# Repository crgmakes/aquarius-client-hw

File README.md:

# Aquarius Client Hardware

All the source files for the client hardware.

# Software 

You will need [KiCad](https://kicad.org) to view and edit this design. Click [here](https://www.kicad.org/download/) to download.

You will also need all the associated libraries and models to drive the design if you want to make changes or view the 3D rendering:

https://github.com/crgmakes/kicad-library.git

Kicad MUST be configured properly to use all the files in this repo. Once you have Kicad installed, under Preferences->Configure Paths..., make the following entries:

1 - KICAD_USER_DIR -> set to the root location of where you placed the above repository.
2 - KICAD_USER_LIBRARY = ${KICAD_USER_DIR}/Library
3 - KICAD_USER_MODEL_DIR = ${KICAD_USER_LIBRARY}/models
4 - KICAD_USER_TEMPLATE_DIR	= ${KICAD_USER_LIBRARY}/templates	

Kicad will operate mostly normally if these are not set properly. You will notice an issue when you view the PCB in 3D mode.

***NOTE***: after makeing a release build in git, if your rendered 3D images are missing components, ensure the path to EVERY component model is set to ${KICAD_USER_MODEL_DIR}/<model name>.

Kicad sometimes replaces the variable with an expansion and that FAILS during the build process because the expanded variable is local and does not match the build environment.

---

THE DESIGN IS PROVIDED "AS IS" AND THE AUTHOR DISCLAIMS ALL WARRANTIES WITH REGARD TO THIS DESIGN INCLUDING ALL IMPLIED WARRANTIES OF MERCHANTABILITY AND FITNESS. IN NO EVENT SHALL THE AUTHOR BE LIABLE FOR ANY SPECIAL, DIRECT, INDIRECT, OR CONSEQUENTIAL DAMAGES OR ANY DAMAGES WHATSOEVER RESULTING FROM LOSS OF USE, DATA OR PROFITS, WHETHER IN AN ACTION OF CONTRACT, NEGLIGENCE OR OTHER TORTIOUS ACTION, ARISING OUT OF OR IN CONNECTION WITH THE USE OR PERFORMANCE OF THIS DESIGN.

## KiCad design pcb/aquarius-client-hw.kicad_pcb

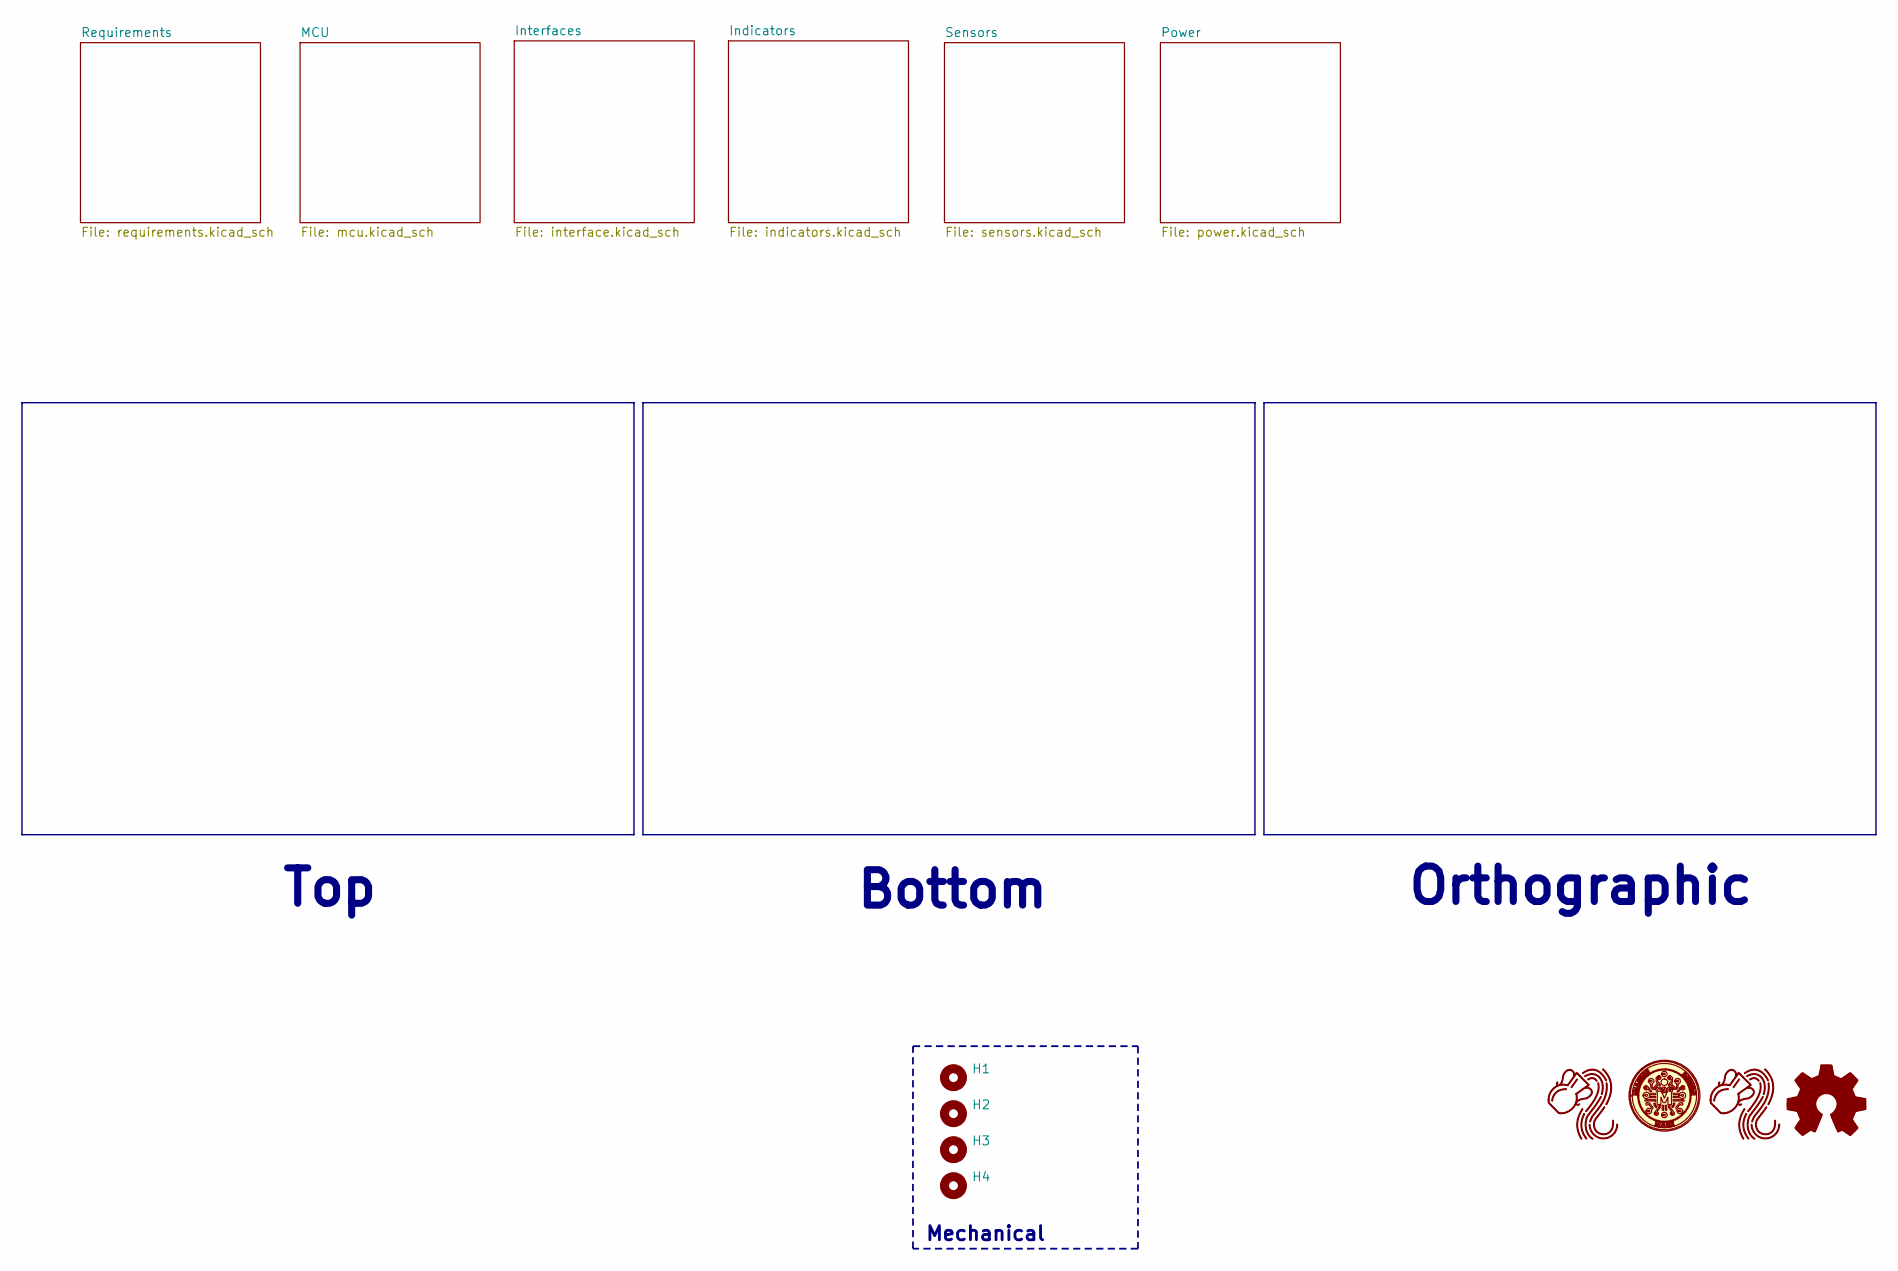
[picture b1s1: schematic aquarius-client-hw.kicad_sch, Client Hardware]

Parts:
H1, H2, H3, H4: MountingHole_3.2mm_M3_Pad_Via
LOGO1: CRGM Logo 5mm
LOGO2, LOGO3: Aquarius Logo 5mm
LOGO4: OSHW-Logo_5.7x6mm_SilkScreen

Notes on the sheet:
Mechanical
Bottom
Orthographic
Top

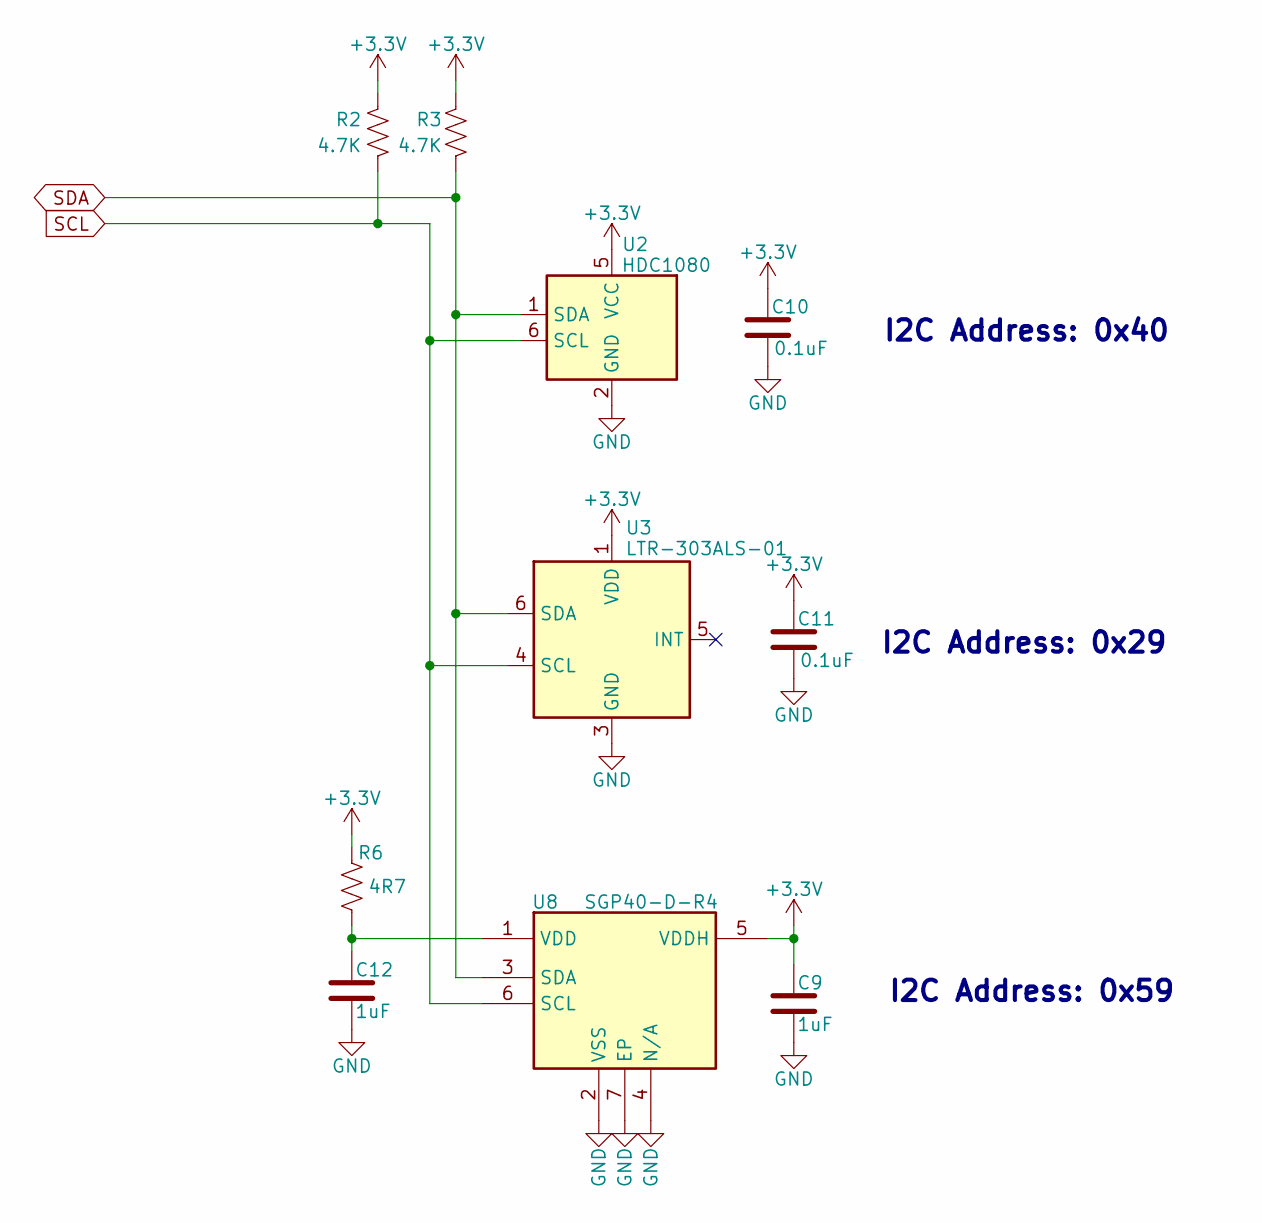
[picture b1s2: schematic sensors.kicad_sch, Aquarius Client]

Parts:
C9, C12: 1uF; C_0603_1608Metric; Tolerance 10%; MPN CGA0603X5R105K160JT; Mouser 187-CL10B105KO8NNNC
C10, C11: 0.1uF; C_0603_1608Metric; Tolerance 10%; MPN CL10B104KO8NNNC; Digikey 1276-1005-2-ND
R2: 4.7K; R_0603_1608Metric; Tolerance 5%; MPN FRC0603J472 TS; Mouser 652-CR0603-JW-472ELF
R3: 4.7K; R_0603_1608Metric; Tolerance 5%; MPN FRC0603J472 TS; LCSC C2907166
R6: 4R7; R_0603_1608Metric; Tolerance 5%; MPN FRC0603J4R7 TS; Mouser 652-CR0603JW-4R7ELF
U2: HDC1080; PWSON-N6; MPN HDC1080DMBR; Digikey 296-46272-2-ND
U3: LTR-303ALS-01; MPN LTR-303ALS-01; Digikey 160-2161-2-ND
U8: SGP40-D-R4; SON80P244X244X95-7N; MPN SGP40-D-R4; Digikey 1649-SGP40-D-R4TR-ND

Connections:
+3.3V: C9.1, C10.1, C11.1, R2.2, R3.2, R6.1, U2.5 (VCC), U3.1 (VDD), U8.5 (VDDH); also elsewhere on the board
GND: C9.2, C10.2, C11.2, C12.2, U2.2 (GND), U3.3 (GND), U8.2 (VSS), U8.4 (N/A), U8.7 (EP); also elsewhere on the board
unnamed: C12.1, R6.2, U8.1 (VDD)
SCL: R2.1, U2.6 (SCL), U3.4 (SCL), U8.6 (SCL); also elsewhere on the board
SDA: R3.1, U2.1 (SDA), U3.6 (SDA), U8.3 (SDA); also elsewhere on the board

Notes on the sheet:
I2C Address: 0x40
I2C Address: 0x29
I2C Address: 0x59

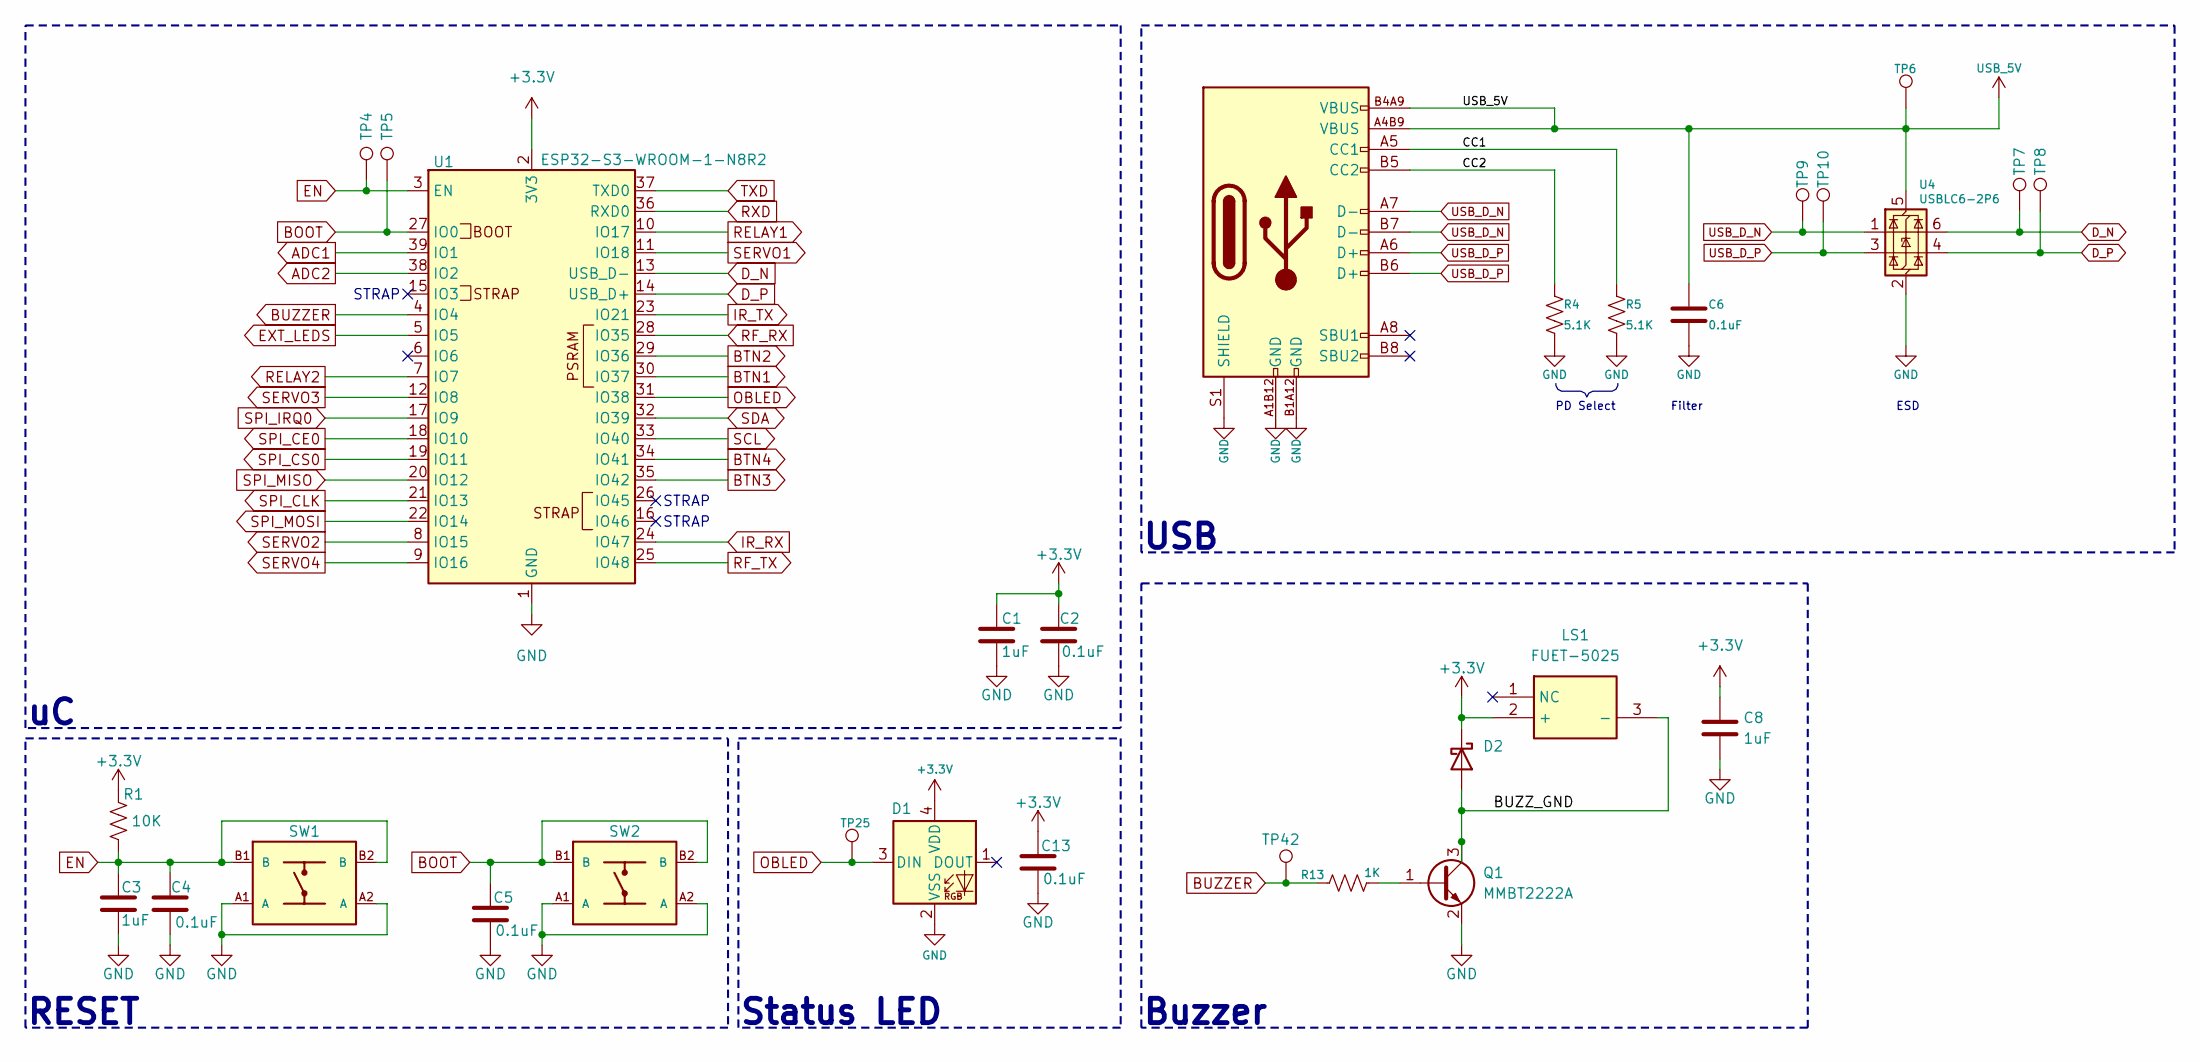
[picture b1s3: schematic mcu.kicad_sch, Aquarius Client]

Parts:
C1, C8: 1uF; C_0603_1608Metric; Tolerance 10%; MPN CGA0603X5R105K160JT; LCSC C6119849
C2, C6: 0.1uF; C_0603_1608Metric; Tolerance 10%; MPN CL10B104KO8NNNC; LCSC C66501
C3: 1uF; C_0603_1608Metric; Tolerance 10%; MPN CGA0603X5R105K160JT; Mouser 187-CL10B105KO8NNNC
C4: 0.1uF; C_0603_1608Metric; Tolerance 10%; MPN CL10B104KO8NNNC; Mouser 187-CL10B104KO8NNNC
C5, C13: 0.1uF; C_0603_1608Metric; Tolerance 10%; MPN CL10B104KO8NNNC; Digikey 1276-1005-2-ND
D1: WS2812B-2020; LED_WS2812B-2020_PLCC4_2.0x2.0mm; MPN WS2812C-2020-V1; LCSC C2976072
D2: D_Schottky; D_SOD-523; MPN MSK4010; LCSC C345958
J3: USB_C_USB2.0_16P; GCT_USB4105-GF-A; MPN USB4105-GF-A-060; Mouser 640-USB4105-GF-A-060
LS1: FUET-5025; MPN FUET-5025; Mouser 490-CMT-0502-75SMTTR
Q1: MMBT2222A; SOT-523; MPN MMBT2222AT-7-F; Mouser 621-MMBT2222AT-F
R1: 10K; R_0603_1608Metric; Tolerance 5%; MPN FRC0603J103TS; Mouser 652-CR0603-JW-103ELF
R4, R5: 5.1K; R_0603_1608Metric; Tolerance 5%; MPN FRC0603J512 TS; Mouser 652-CR0603JW-512ELF
R13: 1K; R_0603_1608Metric; Tolerance 5%; MPN FRC0603J102 TS; LCSC C2907113
SW1, SW2: EVQ-Q2B02W; MPN EVQ-Q2B02W; Mouser 667-EVQ-Q2B02W
TP4, TP5, TP6, TP7, TP8, TP9, TP10, TP25, TP42: TestPoint_Pad_D1.0mm
U1: ESP32-S3-WROOM-1-N8R2; MPN ESP32-S3-WROOM-1-N8R2; Mouser 356-ESP32-S3WRM1N8R2
U4: USBLC6-2P6; SOT-666; MPN USBLC6-2P6; LCSC C2827693

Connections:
+3.3V: C1.1, C2.1, C8.1, C13.1, D1.4 (VDD), D2.1 (K), LS1.2 (+), R1.1, U1.2 (3V3); also elsewhere on the board
/MCU/BUZZ_GND: D2.2 (A), LS1.3 (-), Q1.3 (C)
/MCU/CC1: J3.A5 (CC1), R5.1
/MCU/CC2: J3.B5 (CC2), R4.1
ADC1: U1.39 (IO1); also elsewhere on the board
ADC2: U1.38 (IO2); also elsewhere on the board
BOOT: C5.1, SW2.B1 (B), SW2.B2 (B), TP5.1, U1.27 (IO0)
BTN1: U1.30 (IO37); also elsewhere on the board
BTN2: U1.29 (IO36); also elsewhere on the board
BTN3: U1.35 (IO42); also elsewhere on the board
BTN4: U1.34 (IO41); also elsewhere on the board
BUZZER: R13.1, TP42.1, U1.4 (IO4)
D_N: TP7.1, U1.13 (USB_D-), U4.6 (I/O1)
D_P: TP8.1, U1.14 (USB_D+), U4.4 (I/O2)
EN: C3.1, C4.1, R1.2, SW1.B1 (B), SW1.B2 (B), TP4.1, U1.3 (EN)
EXT_LEDS: U1.5 (IO5); also elsewhere on the board
GND: C1.2, C2.2, C3.2, C4.2, C5.2, C6.2, C8.2, C13.2, D1.2 (VSS), J3.A1B12 (GND), J3.B1A12 (GND), J3.S1 (SHIELD), Q1.2 (E), R4.2, R5.2, SW1.A1 (A), SW1.A2 (A), SW2.A1 (A), SW2.A2 (A), U1.1 (GND), U1.40 (GND), U1.41 (GND), U4.2 (GND); also elsewhere on the board
IR_RX: U1.24 (IO47); also elsewhere on the board
IR_TX: U1.23 (IO21); also elsewhere on the board
unnamed: Q1.1 (B), R13.2
OBLED: D1.3 (DIN), TP25.1, U1.31 (IO38)
RELAY1: U1.10 (IO17); also elsewhere on the board
RELAY2: U1.7 (IO7); also elsewhere on the board
RF_RX: U1.28 (IO35); also elsewhere on the board
RF_TX: U1.25 (IO48); also elsewhere on the board
RXD: U1.36 (RXD0); also elsewhere on the board
SCL: U1.33 (IO40); also elsewhere on the board
SDA: U1.32 (IO39); also elsewhere on the board
SERVO1: U1.11 (IO18); also elsewhere on the board
SERVO2: U1.8 (IO15); also elsewhere on the board
SERVO3: U1.12 (IO8); also elsewhere on the board
SERVO4: U1.9 (IO16); also elsewhere on the board
SPI_CE0: U1.18 (IO10); also elsewhere on the board
SPI_CLK: U1.21 (IO13); also elsewhere on the board
SPI_CS0: U1.19 (IO11); also elsewhere on the board
SPI_IRQ0: U1.17 (IO9); also elsewhere on the board
SPI_MISO: U1.20 (IO12); also elsewhere on the board
SPI_MOSI: U1.22 (IO14); also elsewhere on the board
TXD: U1.37 (TXD0); also elsewhere on the board
USB_5V: C6.1, J3.A4B9 (VBUS), J3.B4A9 (VBUS), TP6.1, U4.5 (VBUS); also elsewhere on the board
USB_D_N: J3.A7 (D-), J3.B7 (D-), TP9.1, U4.1 (I/O1)
USB_D_P: J3.A6 (D+), J3.B6 (D+), TP10.1, U4.3 (I/O2)

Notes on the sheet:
RESET
STRAP
Buzzer
Filter
Status LED
PD Select
ESD
USB

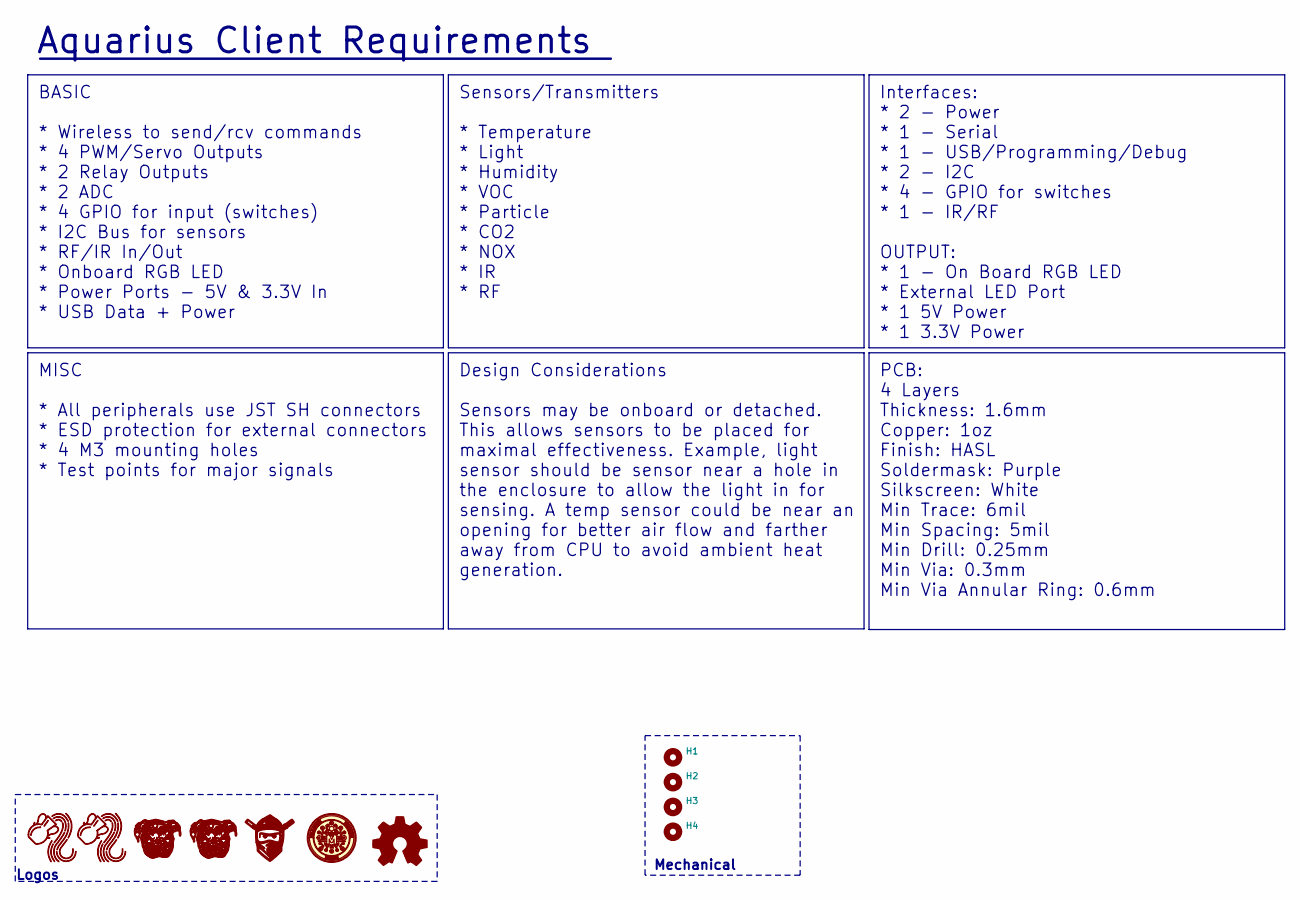
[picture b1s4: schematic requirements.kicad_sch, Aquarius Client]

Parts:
H1, H2, H3, H4: MountingHole_3.2mm_M3_Pad_Via
LOGO1: CRGM Logo 10mm
LOGO2: Aquarius Logo 5mm
LOGO3: Aquarius Logo 8mm
LOGO4: OSHW-Logo_5.7x6mm_SilkScreen
LOGO5: Roxy 6.5mm
LOGO6: Roxy 8mm
LOGO7: FNWW Face 5mm

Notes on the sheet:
Logos
Mechanical
Aquarius Client Requirements
Design Considerations Sensors may be onboard or detached. This allows sensors to be placed for maximal effectiveness. Example, light sensor should be sensor near a hole in the enclosure to allow the light in for sensing. A temp sensor could be near an opening for better air flow and farther away fr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
BASIC * Wireless to send/rcv commands * 4 PWM/Servo Outputs * 2 Relay Outputs * 2 ADC * 4 GPIO for input (switches) * I2C Bus for sensors * RF/IR In/Out * Onboard RGB LED * Power Ports - 5V & 3.3V In * USB Data + Power
Interfaces: * 2 - Power * 1 - Serial * 1 - USB/Programming/Debug * 2 - I2C * 4 - GPIO for switches * 1 - IR/RF OUTPUT: * 1 - On Board RGB LED * External LED Port * 1 5V Power * 1 3.3V Power
MISC * All peripherals use JST SH connectors * ESD protection for external connectors * 4 M3 mounting holes * Test points for major signals
PCB: 4 Layers Thickness: 1.6mm Copper: 1oz Finish: HASL Soldermask: Purple Silkscreen: White Min Trace: 6mil Min Spacing: 5mil Min Drill: 0.25mm Min Via: 0.3mm Min Via Annular Ring: 0.6mm
Sensors/Transmitters * Temperature * Light * Humidity * VOC * Particle * CO2 * NOX * IR * RF

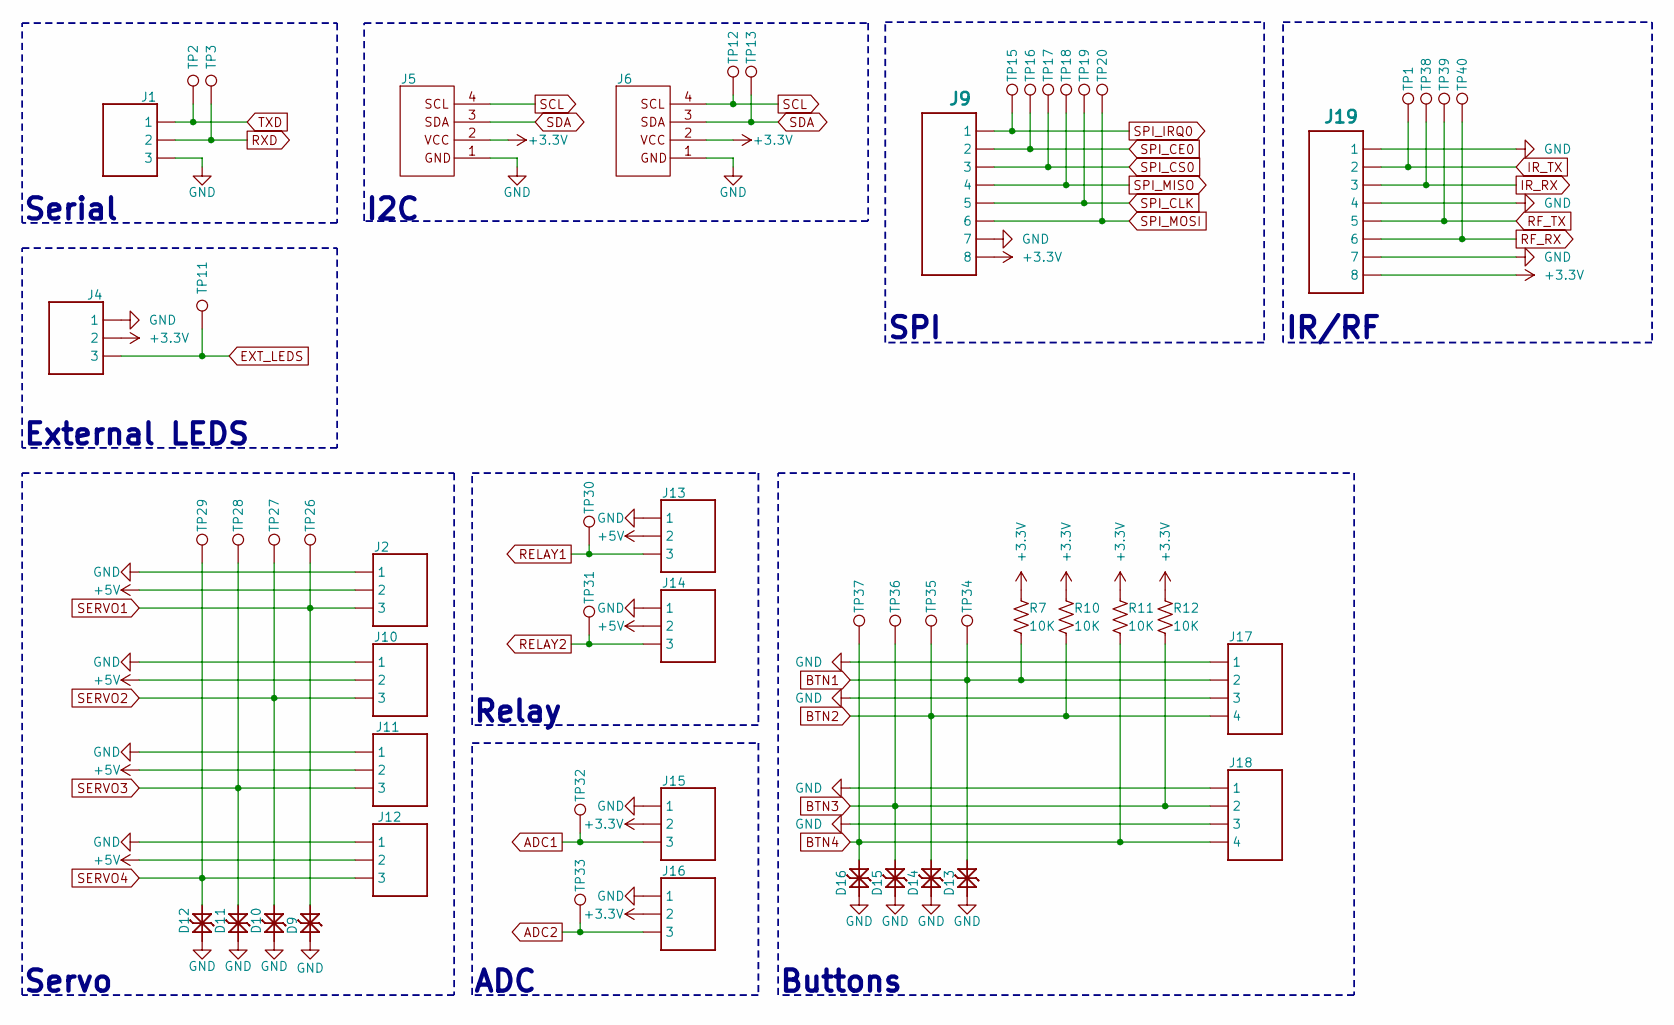
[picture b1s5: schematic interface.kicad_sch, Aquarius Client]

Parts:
D9, D10, D11, D12, D13, D14, D15, D16: PESD5V0S1BB; D_SOD-523; MPN PESD5V0S1BB,115; LCSC C314264
J1, J2, J4, J10, J11, J12, J13, J14, J15, J16: JST_SH_BM03B-SRSS-TB_1x03-1MP_P1.00mm_Vertical; MPN BM03B-SRSS-TB; LCSC C2904985
J5, J6, J17, J18: JST_SH_BM04B-SRSS-TB_1x04-1MP_P1.00mm_Vertical; MPN BM04B-SRSS-TBT(LF)(SN); Mouser 306-BM04BSRSSTBTLFSN
J9, J19: JST_SH_BM08B-SRSS-TB_1x08-1MP_P1.00mm_Vertical; MPN BM08B-SRSS-TB(LF)(SN); LCSC C2845376
R7, R10, R11, R12: 10K; R_0603_1608Metric; Tolerance 5%; MPN FRC0603J103TS; LCSC C2930027
TP1, TP2, TP3, TP11, TP12, TP13, TP15, TP16, TP17, TP18, TP19, TP20, TP26, TP27, TP28, TP29, TP30, TP31, TP32, TP33, TP34, TP35, TP36, TP37, TP38, TP39, TP40: TestPoint_Pad_D1.0mm

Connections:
+3.3V: J4.2, J5.2, J6.2, J9.8, J15.2, J16.2, J19.8, R7.1, R10.1, R11.1, R12.1; also elsewhere on the board
+5V: J2.2, J10.2, J11.2, J12.2, J13.2, J14.2; also elsewhere on the board
ADC1: J15.3, TP32.1; also elsewhere on the board
ADC2: J16.3, TP33.1; also elsewhere on the board
BTN1: D13.2 (K2), J17.2, R7.2, TP34.1; also elsewhere on the board
BTN2: D14.2 (K2), J17.4, R10.2, TP35.1; also elsewhere on the board
BTN3: D15.2 (K2), J18.2, R12.2, TP36.1; also elsewhere on the board
BTN4: D16.2 (K2), J18.4, R11.2, TP37.1; also elsewhere on the board
EXT_LEDS: J4.3, TP11.1; also elsewhere on the board
GND: D9.1 (K1), D10.1 (K1), D11.1 (K1), D12.1 (K1), D13.1 (K1), D14.1 (K1), D15.1 (K1), D16.1 (K1), J1.3, J2.1, J4.1, J5.1, J6.1, J9.7, J10.1, J11.1, J12.1, J13.1, J14.1, J15.1, J16.1, J17.1, J17.3, J18.1, J18.3, J19.1, J19.4, J19.7; also elsewhere on the board
IR_RX: J19.3, TP38.1; also elsewhere on the board
IR_TX: J19.2, TP1.1; also elsewhere on the board
RELAY1: J13.3, TP30.1; also elsewhere on the board
RELAY2: J14.3, TP31.1; also elsewhere on the board
RF_RX: J19.6, TP40.1; also elsewhere on the board
RF_TX: J19.5, TP39.1; also elsewhere on the board
RXD: J1.2, TP3.1; also elsewhere on the board
SCL: J5.4, J6.4, TP12.1; also elsewhere on the board
SDA: J5.3, J6.3, TP13.1; also elsewhere on the board
SERVO1: D9.2 (K2), J2.3, TP26.1; also elsewhere on the board
SERVO2: D10.2 (K2), J10.3, TP27.1; also elsewhere on the board
SERVO3: D11.2 (K2), J11.3, TP28.1; also elsewhere on the board
SERVO4: D12.2 (K2), J12.3, TP29.1; also elsewhere on the board
SPI_CE0: J9.2, TP16.1; also elsewhere on the board
SPI_CLK: J9.5, TP19.1; also elsewhere on the board
SPI_CS0: J9.3, TP17.1; also elsewhere on the board
SPI_IRQ0: J9.1, TP15.1; also elsewhere on the board
SPI_MISO: J9.4, TP18.1; also elsewhere on the board
SPI_MOSI: J9.6, TP20.1; also elsewhere on the board
TXD: J1.1, TP2.1; also elsewhere on the board

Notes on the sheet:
ADC
Serial
External LEDS
Buttons
Servo
IR/RF
Relay
I2C
SPI

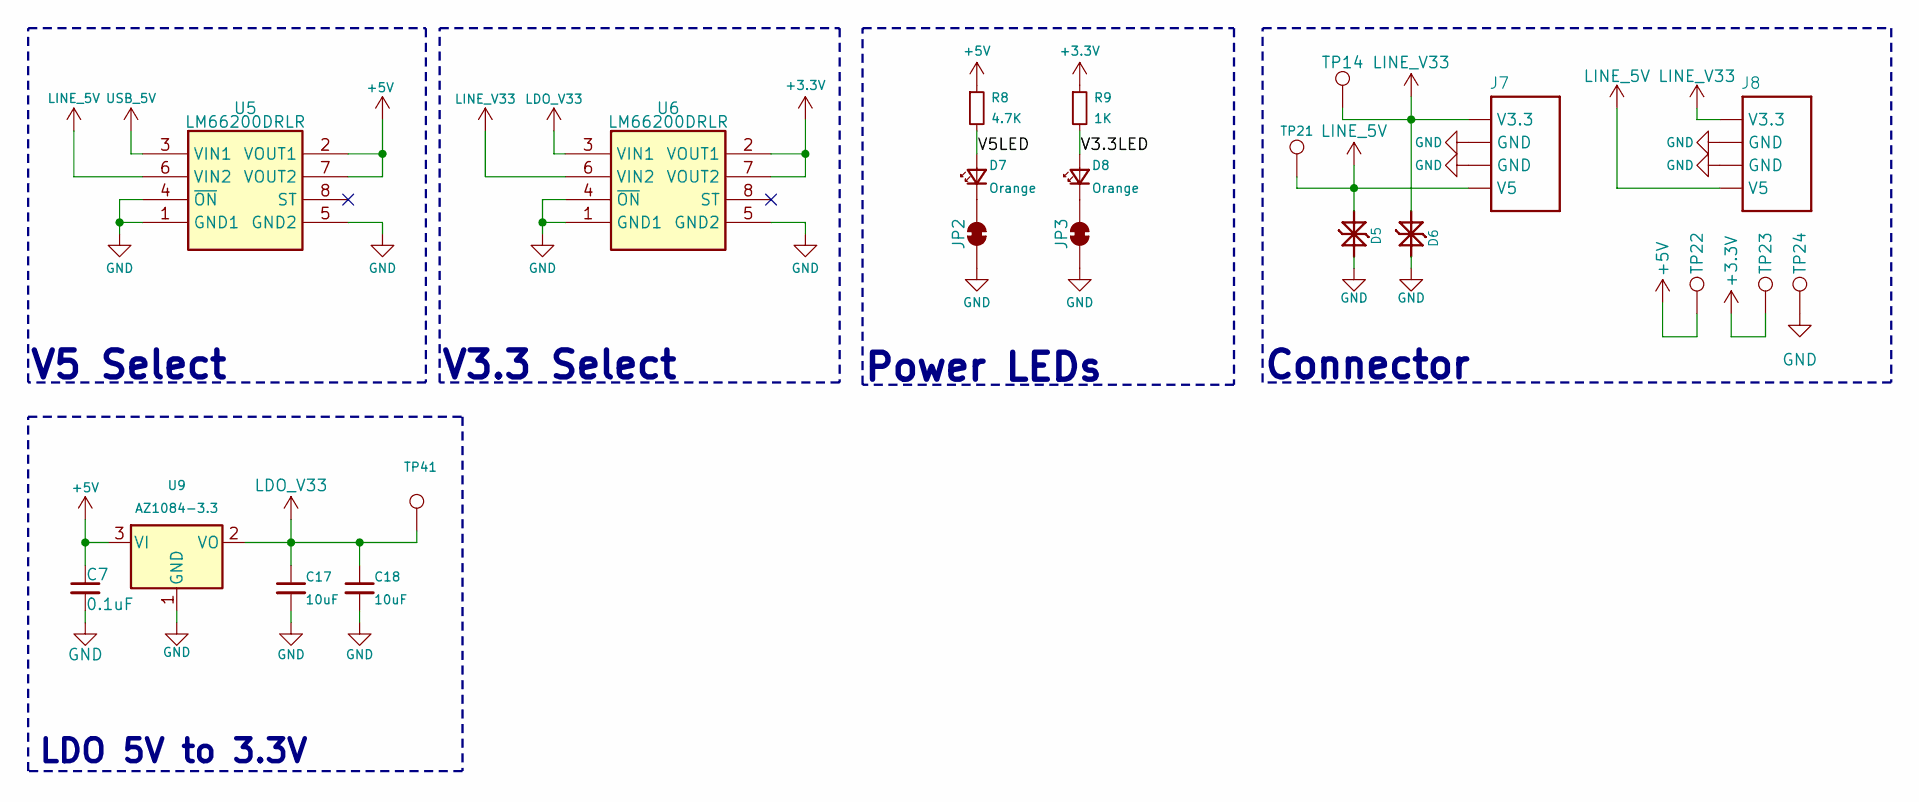
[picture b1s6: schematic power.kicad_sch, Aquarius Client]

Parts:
C7: 0.1uF; C_0603_1608Metric; Tolerance 10%; MPN CL10B104KO8NNNC; LCSC C66501
C17, C18: 10uF; C_0603_1608Metric; Tolerance 10%; MPN CL10A106MO8NQNC; Mouser 187-CL10A106MO8NQNC
D5: PESD5V5C1BL; DFN1006-2; MPN PESD5V5C1BLYL; LCSC C2827636
D6: PESD3V3S1BL; DFN1006-2; MPN LESD8D3.3CAT5G; LCSC C5563754
D7, D8: Orange; LED_0603_1608Metric; MPN XL-1608UOC-06; Mouser 859-LTST-C190KFKT
J7, J8: JST_SH_SM04B-SRSS-TB_1x04-1MP_P1.00mm_Horizontal; MPN SM04B-SRSS-TBT(LF)(SN); LCSC C2763614
JP2, JP3: SolderJumper-2_P1.3mm_Bridged_RoundedPad1.0x1.5mm
R8: 4.7K; R_0603_1608Metric; Tolerance 5%; MPN FRC0603J472 TS; Mouser 652-CR0603-JW-472ELF
R9: 1K; R_0603_1608Metric; Tolerance 5%; MPN FRC0603J102 TS; Mouser 652-CR0603-JW-102ELF
TP14, TP21, TP22, TP23, TP24, TP41: TestPoint_Pad_D1.0mm
U5, U6: LM66200DRLR; SOTFL50P160X60-8N; MPN LM66200DRLR; Mouser 595-LM66200DRLR
U9: AZ1084-3.3; TO-252-2; MPN AZ1084CD-3.3TRG1; Mouser 621-AZ1084CD-3.3TRG1

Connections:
+3.3V: R9.1, TP23.1, U6.2 (VOUT1), U6.7 (VOUT2); also elsewhere on the board
+5V: C7.1, R8.1, TP22.1, U5.2 (VOUT1), U5.7 (VOUT2), U9.3 (VI); also elsewhere on the board
/Power/V3.3LED: D8.2 (A), R9.2
/Power/V5LED: D7.2 (A), R8.2
GND: C7.2, C17.2, C18.2, D5.1 (K1), D6.1 (K1), J7.2 (GND), J7.3 (GND), J8.2 (GND), J8.3 (GND), JP2.1 (A), JP3.1 (A), TP24.1, U5.1 (GND1), U5.4 (~ON), U5.5 (GND2), U6.1 (GND1), U6.4 (~ON), U6.5 (GND2), U9.1 (GND); also elsewhere on the board
LDO_V33: C17.1, C18.1, TP41.1, U6.3 (VIN1), U9.2 (VO)
LINE_5V: D5.2 (K2), J7.1 (V5), J8.1 (V5), TP21.1, U5.6 (VIN2)
LINE_V33: D6.2 (K2), J7.4 (V3.3), J8.4 (V3.3), TP14.1, U6.6 (VIN2)
unnamed: D7.1 (K), JP2.2 (B)
unnamed: D8.1 (K), JP3.2 (B)
USB_5V: U5.3 (VIN1); also elsewhere on the board

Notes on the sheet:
Connector
Power LEDs
V3.3 Select
V5 Select
LDO 5V to 3.3V

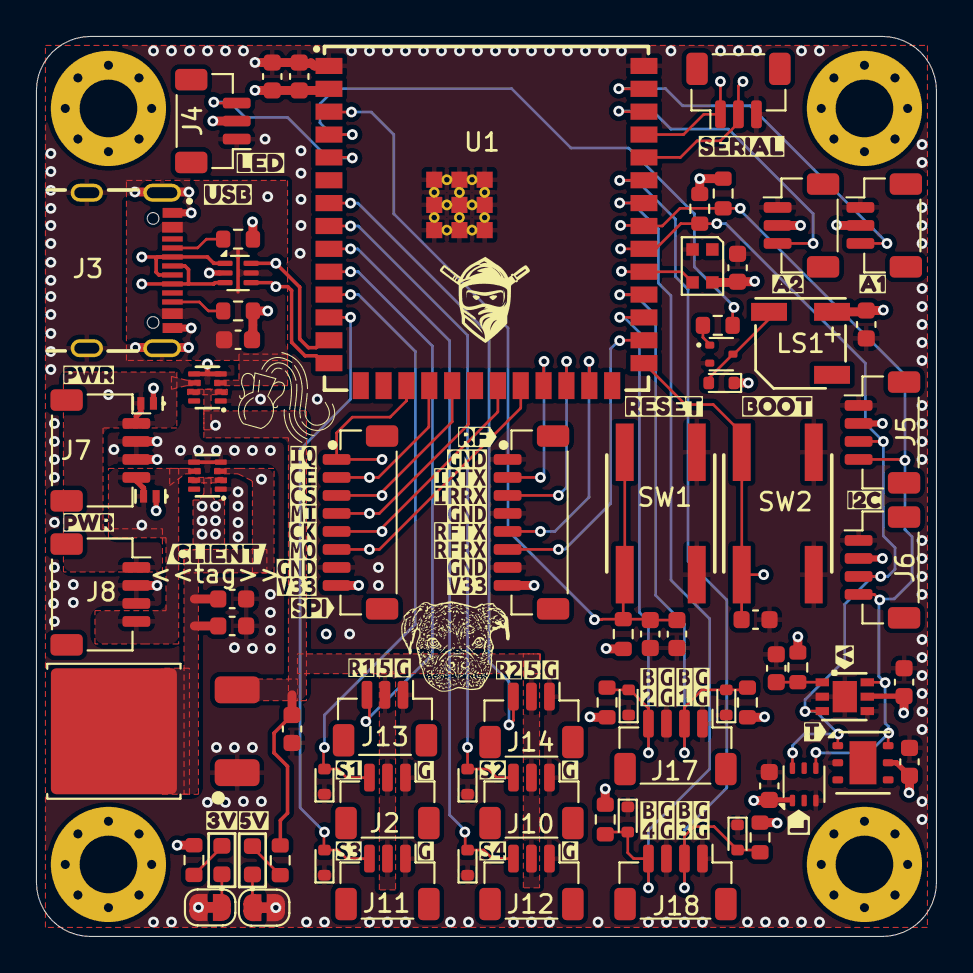
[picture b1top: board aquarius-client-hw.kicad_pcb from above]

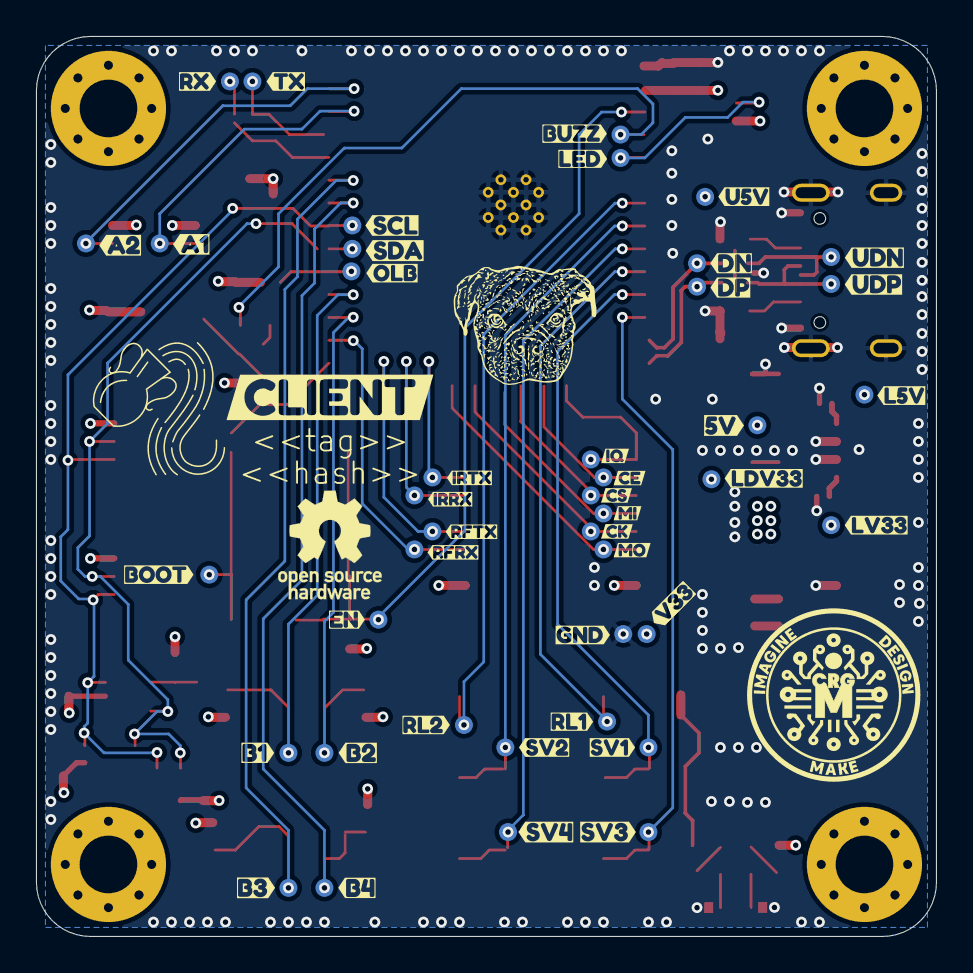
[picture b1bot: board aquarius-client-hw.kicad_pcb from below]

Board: 4 copper layers, 50.0 x 50.0 mm, 227 parts (89 on the bottom side), 51 nets.

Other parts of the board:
kibuzzard-68A7E28F: G***; kibuzzard-68A7E28F
kibuzzard-68A7E307: G***; kibuzzard-68A7E307
kibuzzard-68A7E319: G***; kibuzzard-68A7E319
kibuzzard-68A7E323: G***; kibuzzard-68A7E323
kibuzzard-68A7E330: G***; kibuzzard-68A7E330
kibuzzard-68A7E335: G***; kibuzzard-68A7E335
kibuzzard-68B3A65F: G***; kibuzzard-68B3A65F
kibuzzard-68B3A654: G***; kibuzzard-68B3A654
kibuzzard-68B3AA1F: G***; kibuzzard-68B3AA1F
kibuzzard-68B3AA17: G***; kibuzzard-68B3AA17
kibuzzard-68B3AA32: G***; kibuzzard-68B3AA32
kibuzzard-68B3AC3B: G***; kibuzzard-68B3AC3B
kibuzzard-68B3AC4B: G***; kibuzzard-68B3AC4B
kibuzzard-68B3AC5A, kibuzzard-68B3AC5A#2: G***; kibuzzard-68B3AC5A
kibuzzard-68B3AC9E: G***; kibuzzard-68B3AC9E
kibuzzard-68B3AC33: G***; kibuzzard-68B3AC33
kibuzzard-68B3AC43: G***; kibuzzard-68B3AC43
kibuzzard-68B3AC53: G***; kibuzzard-68B3AC53
kibuzzard-68B3AC63: G***; kibuzzard-68B3AC63
kibuzzard-68B3ACA6: G***; kibuzzard-68B3ACA6
kibuzzard-68B3ACAD: G***; kibuzzard-68B3ACAD
kibuzzard-68B3ACBE: G***; kibuzzard-68B3ACBE
kibuzzard-68B3ACD0: G***; kibuzzard-68B3ACD0
kibuzzard-68B3ACDE: G***; kibuzzard-68B3ACDE
kibuzzard-68B3ACEE: G***; kibuzzard-68B3ACEE
kibuzzard-68B3ACFB: G***; kibuzzard-68B3ACFB
kibuzzard-68B3ADFB: G***; kibuzzard-68B3ADFB
kibuzzard-68B36A6C: G***; kibuzzard-68B36A6C
kibuzzard-68B65F3B: G***; kibuzzard-68B65F3B
kibuzzard-68B65F21: G***; kibuzzard-68B65F21
kibuzzard-68B65F32: G***; kibuzzard-68B65F32
kibuzzard-68B65F42: G***; kibuzzard-68B65F42
kibuzzard-68B65FD7: G***; kibuzzard-68B65FD7
kibuzzard-68B65FE2: G***; kibuzzard-68B65FE2
kibuzzard-68B65FE9: G***; kibuzzard-68B65FE9
kibuzzard-68B65FF0: G***; kibuzzard-68B65FF0
kibuzzard-68B366B4: G***; kibuzzard-68B366B4
kibuzzard-68B368E2: G***; kibuzzard-68B368E2
kibuzzard-68B368ED: G***; kibuzzard-68B368ED
kibuzzard-68B368FE: G***; kibuzzard-68B368FE
kibuzzard-68B662DC: G***; kibuzzard-68B662DC
kibuzzard-68B662E3: G***; kibuzzard-68B662E3
kibuzzard-68B662EF: G***; kibuzzard-68B662EF
kibuzzard-68B662F4: G***; kibuzzard-68B662F4
kibuzzard-68B662FC: G***; kibuzzard-68B662FC
kibuzzard-68B3677E: G***; kibuzzard-68B3677E
kibuzzard-68B6602D: G***; kibuzzard-68B6602D
kibuzzard-68B6603D: G***; kibuzzard-68B6603D
kibuzzard-68B6630C: G***; kibuzzard-68B6630C
kibuzzard-68B36906: G***; kibuzzard-68B36906
kibuzzard-68B66007: G***; kibuzzard-68B66007
kibuzzard-68B66036: G***; kibuzzard-68B66036
kibuzzard-68B66042: G***; kibuzzard-68B66042
kibuzzard-68B66048: G***; kibuzzard-68B66048
kibuzzard-68B66302: G***; kibuzzard-68B66302
kibuzzard-68B66307: G***; kibuzzard-68B66307
kibuzzard-68BB9AB6: G***; kibuzzard-68BB9AB6
kibuzzard-68BB9ABD: G***; kibuzzard-68BB9ABD
kibuzzard-68BB9B03: G***; kibuzzard-68BB9B03
kibuzzard-68BC2B7D: G***; kibuzzard-68BC2B7D
kibuzzard-68BC3B7F: G***; kibuzzard-68BC3B7F
kibuzzard-68BC3B9C: G***; kibuzzard-68BC3B9C
kibuzzard-68BC3BAC: G***; kibuzzard-68BC3BAC
kibuzzard-68BC3EA3: G***; kibuzzard-68BC3EA3
kibuzzard-68BC3EAA: G***; kibuzzard-68BC3EAA
kibuzzard-68BC29E0: G***; kibuzzard-68BC29E0
kibuzzard-68BC210E: G***; kibuzzard-68BC210E
kibuzzard-68BC211C: G***; kibuzzard-68BC211C
kibuzzard-68BC213E: G***; kibuzzard-68BC213E
kibuzzard-68BC215D: G***; kibuzzard-68BC215D
kibuzzard-68BC217F: G***; kibuzzard-68BC217F
kibuzzard-68BC218D: G***; kibuzzard-68BC218D
kibuzzard-68BC2102: G***; kibuzzard-68BC2102
kibuzzard-68BC2127: G***; kibuzzard-68BC2127
kibuzzard-68BC2137: G***; kibuzzard-68BC2137
kibuzzard-68BC2167: G***; kibuzzard-68BC2167
kibuzzard-68BC2179: G***; kibuzzard-68BC2179
kibuzzard-68BC2187: G***; kibuzzard-68BC2187
kibuzzard-68BC2328: G***; kibuzzard-68BC2328
kibuzzard-689A6C29: G***; kibuzzard-689A6C29
kibuzzard-690A7D58: G***; kibuzzard-690A7D58
kibuzzard-6812E3A0: G***; kibuzzard-6812E3A0
kibuzzard-6812E3AD: G***; kibuzzard-6812E3AD
kibuzzard-6812E3BB: G***; kibuzzard-6812E3BB
kibuzzard-6812E3C5: G***; kibuzzard-6812E3C5
kibuzzard-6812E37E: G***; kibuzzard-6812E37E
kibuzzard-6812E420: G***; kibuzzard-6812E420
kibuzzard-6894D76E: G***; kibuzzard-6894D76E
kibuzzard-68927E88: G***; kibuzzard-68927E88
kibuzzard-68927E94: G***; kibuzzard-68927E94
kibuzzard-68927EA7: G***; kibuzzard-68927EA7
kibuzzard-68927EAF: G***; kibuzzard-68927EAF
kibuzzard-68953D9F: G***; kibuzzard-68953D9F
kibuzzard-68953DBA: G***; kibuzzard-68953DBA
kibuzzard-68953DE5: G***; kibuzzard-68953DE5
kibuzzard-68953DED: G***; kibuzzard-68953DED
kibuzzard-68953E7E: G***; kibuzzard-68953E7E
kibuzzard-68953F10: G***; kibuzzard-68953F10

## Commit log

2025-07-13 Initial checkin
2025-07-24 Updated license and implemented RP2040
2025-08-11 Added interfaces and fully routed PCB
2025-08-12 Change schematic name
2025-08-12 Changed name to client
2025-08-12 Updated project name and properties
2025-08-12 Added labels for LEDs
2025-08-12 Fixed offset for connectors
2025-08-14 Changed git runner to use central file
2025-08-14 Updated git runner file
2025-08-16 Switch cap/res to CRGM footprint
2025-08-22 Added button inputs and pull ups
2025-08-23 Updated git script
2025-08-25 Added renders and aligned connectors
    Added renders
    Aligned connectors to grid
    Added dimensions
    Fixed part numbers and values
2025-08-26 Updated descriptions; fixed MN
2025-08-26 Updated user model directory
2025-08-28 Fixed title name and panel props
    * Fixed title name
    * Fixed panel props
    * Updated descriptions
    * Updated fab properties
2025-08-28 fixed model error
2025-08-28 fixed path to model for SM04B
2025-08-28 removed plane rectange from user comments
2025-08-28 Updated stackup and fab drawing
2025-08-31 Added RF connector; re-placed and re-routed
2025-08-31 Fixed model for LDO; fixed renders on main page
2025-09-01 Removed indictors sheet
    Fixed attribute consistency with schematic and symbols
    Moved logos to separate box
    Updated DRC warnings/ignore
2025-09-02 Added dimensions
2025-09-02 Changed panel to 1x1
2025-09-06 Cleaned fab layer.
2025-09-06 Added buzzer
    Added buzzer
    Fixed models
    Updated images
2025-09-06 Added buzzer; fixed models
    Updated renders
2025-09-08 Updated part attributes for consistency
2025-09-09 fixed LCSC part numbers
2025-10-22 Minor project view setting changes
2025-10-26 Updated .gitignore
2025-11-02 Updated LTR address to 0x40 rather than 0x80
2025-11-05 Updated LED footprint
2026-03-01 replaced .wrl with .step
